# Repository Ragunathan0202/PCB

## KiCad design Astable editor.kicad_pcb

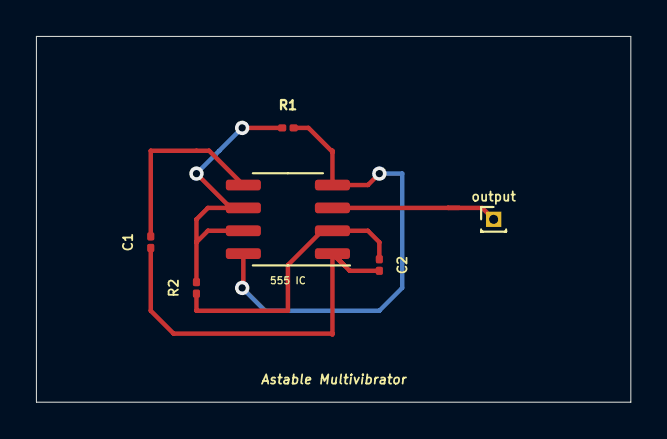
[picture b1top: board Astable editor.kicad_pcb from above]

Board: 2 copper layers, 33.0 x 20.3 mm, 6 parts (0 on the bottom side), 6 nets.

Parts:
555 IC: 555; SOIC-8_3.9x4.9mm_P1.27mm
C1: 0.01uF; C_0201_0603Metric
C2: 0.1uF; C_0201_0603Metric
R1, R2: 10k; R_0201_0603Metric
output: output; PinHeader_1x01_P1.00mm_Vertical

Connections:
GND: 555 IC.1, C1.2, C2.2
unnamed: 555 IC.5, C1.1
unnamed: 555 IC.2, C2.1, R2.2
unnamed: 555 IC.6, 555 IC.7, R1.2, R2.1
unnamed: 555 IC.3, output.1
VCC: 555 IC.4, 555 IC.8, R1.1

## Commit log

2021-08-22 Create Astable
